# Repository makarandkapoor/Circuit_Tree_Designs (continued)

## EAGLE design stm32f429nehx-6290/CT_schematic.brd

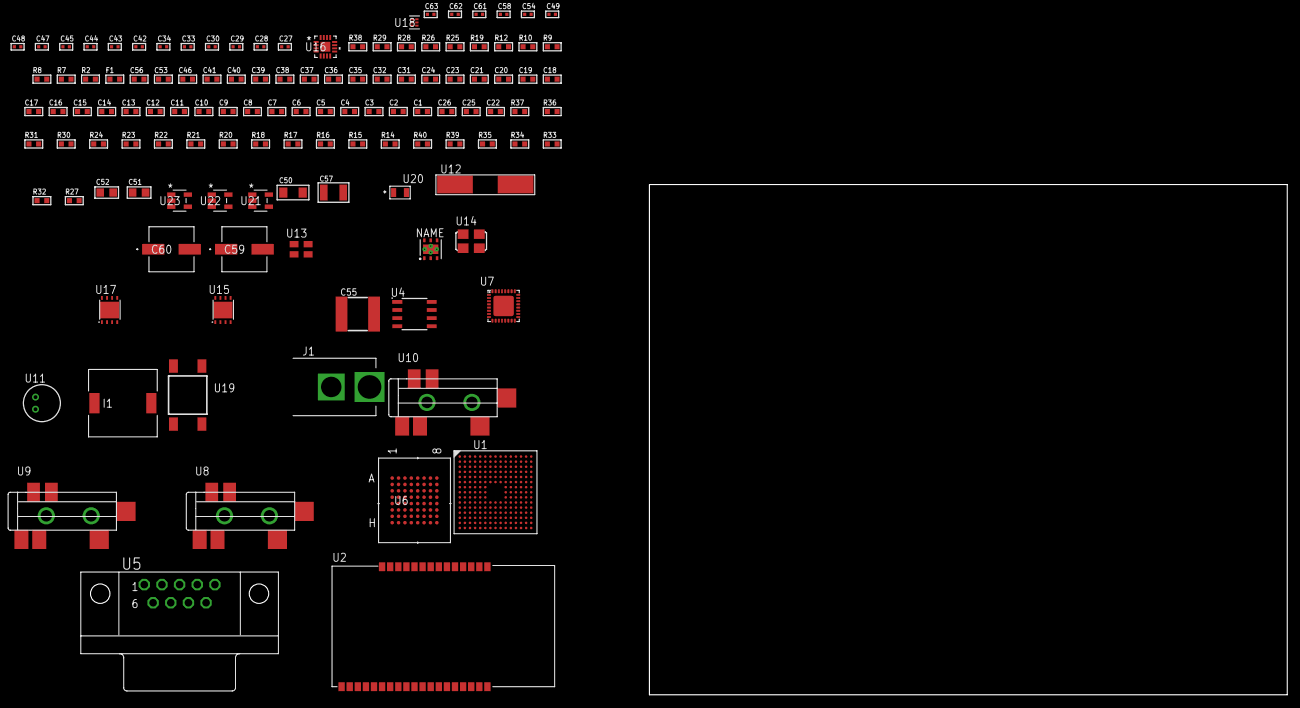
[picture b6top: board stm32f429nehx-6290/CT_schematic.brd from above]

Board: 2 copper layers, 100.0 x 80.0 mm, 122 parts (0 on the bottom side), 109 nets, no tracks yet.

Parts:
C1, C24, C31, C32, C35, C36, C37, C38, C39, C40, C41, C46, C53, C56: 1e-06; C0603
C2, C3, C4, C5, C6, C7, C8, C9, C10, C11, C12, C13, C14, C15, C16, C17, C18, C19, C20, C21: 1e-07; C0603
C22: 4.7e-06; C0603
C23: 1e-08; C0603
C25, C26: 2.2e-06; C0603
C27, C28: 1e-11; C0402
C29, C42, C43, C44, C45, C54, C58: 1e-07; C0402
C30, C33, C34, C47, C48, C49, C61, C62, C63: 1e-08; C0402
C50: 1e-05; C1206
C51, C52: 1e-05; C0805
C55: 6.8e-05; 2220
C57: 1e-05; C1210
C59, C60: 0.0001; EXV-9H
F1: 240.0; L0603
I1: 3.8e-06; DR1040
J1: PJ-037B; PJ-037B_PACKAGE
R2, R29: 1000.0; R0603
R7, R8, R9: 4700.0; R0603
R10, R12: 2200.0; R0603
R14, R15, R16, R17, R18, R20, R21, R22, R23, R24, R36, R37: 10000.0; R0603
R19: 120.0; R0603
R25, R26: 1270.0; R0603
R27, R33, R35: 100000.0; R0603
R28: 200.0; R0603
R30: 20000.0; R0603
R31: 91000.0; R0603
R32, R34: 300000.0; R0603
R38: 9100.0; R0603
R39: 680000.0; R0603
R40: 120000.0; R0603
U1: STM32F429NEH6; TFBGA216
U2: ETRX3587
U3: HDC1080DMBR; WSON-6
U4: MCP2562-E/SN; SOIC-8
U5: 182-009-113R531; 182-009-MALE
U6: mt28ew512aba1HPC-0AAT; LBGA-64
U7: SGTL5000XNAA3; QFN-32
U8, U9, U10: SJ-43515TS-SMT-TR
U11: WM-64PCT; WM-64PC
U12: ABLS-25.000MHZ-B2F-T
U13: ASEK-32.768KHz-ECST; ASEK
U14: ASFL-24.57MHZ-NCS; ASFL1
U15: LP3878SDX-ADJ/NOPB; WSON-8
U16: LTC3601EUD#PBF; QFN-16_EP
U17: LP2951ACSDX/NOPB; WSON-8
U18: TPS3895ADRYR; SON-6
U19: 4-1437565-2; SW_4-1437565-2
U20: Q65110A2395; LGM67K-G1J2-24-Z
U21, U22, U23: nc7sz125m5x; NC7SZ125M5X

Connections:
CLK_CRYSTAL_U1_G1: C27.1, U1.G1, U12.1
CLK_CRYSTAL_U1_H1: C28.1, U1.H1, U12.2
CLK_U1_E1: U1.E1, U13.3
CLK_U7_21: U7.21, U14.3
GND: C1.2, C2.2, C3.2, C4.2, C5.2, C6.2, C7.2, C8.2, C9.2, C10.2, C11.2, C12.2, C13.2, C14.2, C15.2, C16.2, C17.2, C18.2, C19.2, C20.2, C21.2, C22.2, C23.2, C24.2, C25.2, C26.2, C27.2, C28.2, C29.2, C30.2, C31.2, C32.2, C33.2, C34.2, C42.2, C43.2, C44.2, C45.2, C46.2, C47.2, C48.2, C49.2, C50.2, C51.2, C52.2, C53.2, C55.1, C55.2, C56.2, C57.2, C58.2, C59.2, C60.2, C61.2, C62.2, C63.2, J1.2, R2.2, R16.2, R17.2, R18.2, R26.2, R29.2, R30.2, R32.2, R35.2, R38.2, R40.2, U1.F2, U1.F6, U1.F7, U1.F8, U1.F9, U1.F10, U1.G6, U1.G10, U1.H6, U1.H10, U1.J6, U1.J10, U1.K6, U1.K7, U1.K8, U1.K9, U1.K10, U1.L6, U1.M1, U1.N1, U2.1, U2.13, U2.19, U2.20, U2.31, U2.33, U3.2, U3.PAD, U4.2, U4.8, U5.5, U6.E8, U6.H2, U6.H7, U7.1, U7.3, U7.7, U7.EXP, U9.1, U10.1, U11.2, U13.2, U14.2, U15.3, U15.PAD, U16.1, U16.9, U16.17, U17.3, U17.4, U17.PAD, U18.2, U20.C, U21.1, U21.3, U22.1, U22.3, U23.1, U23.3
NET_U1_A7: R10.1, U1.A7, U3.6
NET_U1_B4: R12.1, U1.B4, U3.1
NET_U1_E5: R14.1, U1.E5
NET_U1_E6: R15.1, U1.E6
NET_U1_E11: C26.1, U1.E11
NET_U1_J1: R9.1, U1.J1, U23.4
NET_U1_L5: R17.1, U1.L5
NET_U1_L11: C25.1, U1.L11
NET_U1_M5: R16.1, U1.M5
NET_U1_R1: C23.1, C24.1, F1.1, U1.P1, U1.R1
NET_U1_R15: U19.3, U19.4
NET_U2_7: R8.1, U2.7, U22.4
NET_U2_21: R18.1, U2.21
NET_U4_6: R19.2, U4.6
NET_U5_2: R19.2, U4.6, U5.2
NET_U5_3: R19.1, U4.7, U5.3
NET_U6_B4: R23.1, U6.B4
NET_U6_B5: R7.1, U6.B5, U21.4
NET_U7_10: C45.1, U7.10
NET_U7_29: R25.1, U7.29
NET_U7_31: R26.1, U7.31
NET_U8_1: U7.4, U8.1
NET_U8_2: U7.2, U8.2
NET_U8_5: U7.6, U8.5
NET_U9_2: C36.1, U9.2
NET_U9_5: C35.1, U9.5
NET_U10_2: C38.1, C39.1, U10.2
NET_U10_5: C37.1, U10.5
NET_U10_13: C38.2, C39.2
NET_U11_1: C40.1, C41.1, C46.1, U7.16, U11.1
NET_U11_15: C40.2, C41.2
NET_U15_1: C49.1, U15.1
NET_U15_6: R28.2, R29.1, U15.6
NET_U15_8: R27.1, U15.8
NET_U16_3: C54.2, I1.1, U16.3, U16.4
NET_U16_6: C54.1, U16.6
NET_U16_7: C53.1, U16.7, U16.12
NET_U16_10: R32.1, U16.10
NET_U16_11: R30.1, R31.1, U16.11
NET_U16_ATNET_3: I1.2, R31.2
NET_U17_5: R33.1, U17.5
NET_U17_7: R34.2, R35.1, U17.7
NET_U18_1: R37.1, R38.1, U18.1
NET_U18_3: R39.2, R40.1, U18.3
NET_U18_4: R36.1, U18.4, U21.2, U22.2, U23.2
NET_U19_1: R2.1, U19.1, U19.2
PROC_CAN1_RX: U1.C15, U4.4
PROC_CAN1_TX: U1.B15, U4.1
PROC_FMC_A0: U1.D2, U6.E2
PROC_FMC_A1: U1.E2, U6.D2
PROC_FMC_A2: U1.G2, U6.C2
PROC_FMC_A3: U1.H2, U6.A2
PROC_FMC_A4: U1.J2, U6.B2
PROC_FMC_A5: U1.K3, U6.D3
PROC_FMC_A6: U1.M6, U6.C3
PROC_FMC_A7: U1.N6, U6.A3
PROC_FMC_A8: U1.P6, U6.B6
PROC_FMC_A9: U1.M8, U6.A6
PROC_FMC_A10: U1.N7, U6.C6
PROC_FMC_A11: U1.M7, U6.D6
PROC_FMC_A12: U1.M13, U6.B7
PROC_FMC_A13: U1.M12, U6.A7
PROC_FMC_A14: U1.N12, U6.C7
PROC_FMC_A15: U1.N11, U6.D7
PROC_FMC_A16: U1.N10, U6.E7
PROC_FMC_A17: U1.M10, U6.B3
PROC_FMC_A18: U1.M11, U6.C4
PROC_FMC_A19: U1.A2, U6.D5
PROC_FMC_A20: U1.A1, U6.D4
PROC_FMC_A21: U1.B1, U6.C5
PROC_FMC_A22: U1.B2, U6.B8
PROC_FMC_A23: U1.A3, U6.C8
PROC_FMC_A24: U1.B3, U6.F8
PROC_FMC_D0: U1.L12, U6.E3
PROC_FMC_D1: U1.K13, U6.H3
PROC_FMC_D2: U1.B12, U6.E4
PROC_FMC_D3: U1.C12, U6.H4
PROC_FMC_D4: U1.R8, U6.H5
PROC_FMC_D5: U1.N9, U6.E5
PROC_FMC_D6: U1.P9, U6.H6
PROC_FMC_D7: U1.R9, U6.E6
PROC_FMC_D8: U1.P10, U6.F3
PROC_FMC_D9: U1.R10, U6.G3
PROC_FMC_D10: U1.R12, U6.F4
PROC_FMC_D11: U1.P11, U6.G4
PROC_FMC_D12: U1.R11, U6.F5
PROC_FMC_D13: U1.L15, U6.G6
PROC_FMC_D14: U1.L14, U6.F6
PROC_FMC_D15: U1.K15, U6.G7
PROC_FMC_NBL0: R24.1, U1.A6, U6.F7
PROC_FMC_NE2: R20.1, U1.D9, U6.F2
PROC_FMC_NOE: R21.1, U1.D11, U6.G2
PROC_FMC_NWAIT: U1.B11, U6.A4
PROC_FMC_NWE: R22.1, U1.C10, U6.A5
PROC_I2S2_CK: U1.C11, U7.24
PROC_I2S2_EXT_SD: U1.C14, U7.25
PROC_I2S2_SD: U1.C13, U7.26
PROC_I2S2_WS: U1.E14, U7.23
PROC_UART4_RX: U1.B13, U2.17
PROC_UART4_TX: U1.B14, U2.18
VCC_S1_9V2: C50.1, C52.1, C56.1, C59.1, C60.1, J1.1, R27.2, U15.4, U16.15, U16.16, U17.8
VCC_TIER1_1V2: C42.1, C51.1, R28.1, U7.30, U15.5
VCC_TIER1_3V3: C1.1, C2.1, C3.1, C4.1, C5.1, C6.1, C7.1, C8.1, C9.1, C10.1, C11.1, C12.1, C13.1, C14.1, C15.1, C16.1, C17.1, C18.1, C19.1, C20.1, C21.1, C22.1, C29.1, C30.1, C32.1, C33.1, C34.1, C43.1, C44.1, C47.1, C48.1, C55.2, C58.1, C61.1, C62.1, C63.1, F1.2, I1.2, R7.2, R8.2, R9.2, R10.2, R12.2, R14.2, R15.2, R20.2, R21.2, R22.2, R23.2, R24.2, R25.2, R31.2, R36.2, R37.2, R39.1, U1.C1, U1.E7, U1.E8, U1.E9, U1.E10, U1.F4, U1.F5, U1.F11, U1.G5, U1.G11, U1.H5, U1.H11, U1.J5, U1.J11, U1.K5, U1.K11, U1.L7, U1.L8, U1.L9, U1.L10, U2.32, U3.5, U4.5, U6.D8, U6.F1, U6.G5, U7.5, U7.20, U13.4, U14.4, U16.8, U18.6, U21.5, U22.5, U23.5
VCC_TIER1_5V0: C31.1, C57.1, R33.2, R34.1, U4.3, U17.1

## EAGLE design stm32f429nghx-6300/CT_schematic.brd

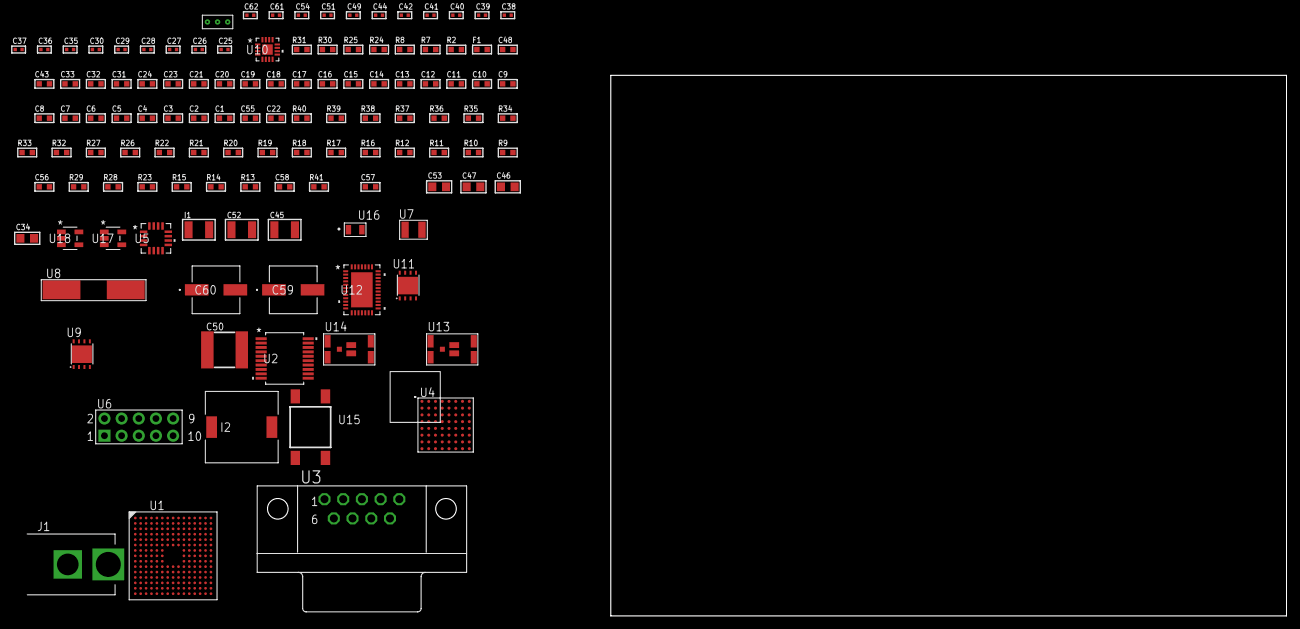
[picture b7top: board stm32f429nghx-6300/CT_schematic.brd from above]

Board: 2 copper layers, 100.0 x 80.0 mm, 121 parts (0 on the bottom side), 121 nets, no tracks yet.

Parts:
C1, C24, C31, C32, C33, C43, C48: 1e-06; C0603
C2, C3, C4, C5, C6, C7, C8, C9, C10, C11, C12, C13, C14, C15, C16, C17, C18, C19, C20, C21: 1e-07; C0603
C22: 4.7e-06; C0603
C23: 1e-08; C0603
C25, C26, C35, C37, C39, C41, C42, C49, C54: 1e-07; C0402
C27, C28, C29, C30: 1e-11; C0402
C34: 4.7e-06; C0805
C36, C38, C40, C44, C51, C61, C62: 1e-08; C0402
C45, C52: 1e-05; C1210
C46, C47, C53: 1e-05; C0805
C50: 6.8e-05; 2220
C55: 2.2e-06; C0603
C56: 2.45e-08; R0603
C57: 2.8258362168397e-09; R0603
C58: 7.105e-09; R0603
C59, C60: 0.0001; EXV-9H
F1: 240.0; L0603
I1: 1.5e-05; L1210
I2: 5.2e-06; DR1040
J1: PJ-037B; PJ-037B_PACKAGE
R2, R25, R31: 1000.0; R0603
R7, R8: 4700.0; R0603
R9, R10, R11, R12, R16, R17, R18, R19, R20, R21, R22, R32, R34, R35, R38, R39, R40: 10000.0; R0603
R13, R14, R15, R23, R29: 100000.0; R0603
R24, R30: 200.0; R0603
R26: 20000.0; R0603
R27: 62000.0; R0603
R28: 300000.0; R0603
R33: 75000.0; R0603
R36, R37: 95300.0; R0603
R41: 111363.63636364; R0603
U1: STM32F429NGH6; TFBGA216
U2: MAX3218EAP+T; SSOP-20
U3: 182-009-113R531; 182-009-MALE
U4: PC28F512P33BFD
U5: TSC2046IRGVR; VQFN-16
U6: HTSS-105-01-G-D
U7: ABS07-32.768KHZ-7-T
U8: ABLS-25.000MHZ-B2F-T
U9, U11: LP3878SDX-ADJ/NOPB; WSON-8
U10: LTC3601EUD#PBF; QFN-16_EP
U12: LTC2928CUHF#PBF; QFN-38_UHF
U13, U14: IRF8306MTRPbF; IRF8306MTRPBF
U15: 4-1437565-2; SW_4-1437565-2
U16: Q65110A2395; LGM67K-G1J2-24-Z
U17, U18: nc7sz125m5x; NC7SZ125M5X
U19: Dummy; DUMMY_PACKAGE_254

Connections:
CLK_CRYSTAL_U1_E1: C27.1, U1.E1, U7.1
CLK_CRYSTAL_U1_F1: C28.1, U1.F1, U7.2
CLK_CRYSTAL_U1_G1: C29.1, U1.G1, U8.1
CLK_CRYSTAL_U1_H1: C30.1, U1.H1, U8.2
GND: C1.2, C2.2, C3.2, C4.2, C5.2, C6.2, C7.2, C8.2, C9.2, C10.2, C11.2, C12.2, C13.2, C14.2, C15.2, C16.2, C17.2, C18.2, C19.2, C20.2, C21.2, C22.2, C23.2, C24.2, C25.2, C26.2, C27.2, C28.2, C29.2, C30.2, C31.2, C32.2, C33.2, C35.2, C36.2, C37.2, C38.2, C39.2, C40.2, C41.2, C42.2, C43.2, C44.2, C45.2, C46.2, C47.2, C48.2, C50.1, C50.2, C51.2, C52.2, C53.2, C54.2, C55.2, C56.2, C57.2, C58.2, C59.2, C60.2, C61.2, C62.2, J1.2, R2.2, R11.2, R25.2, R26.2, R28.2, R31.2, R33.2, R36.2, R37.2, R38.2, R39.2, R40.2, U1.F2, U1.F6, U1.F7, U1.F8, U1.F9, U1.F10, U1.G6, U1.G10, U1.H6, U1.H10, U1.J6, U1.J10, U1.K6, U1.K7, U1.K8, U1.K9, U1.K10, U1.L6, U1.M1, U1.N1, U2.5, U2.17, U2.20, U3.5, U4.B2, U4.H2, U4.H4, U4.H6, U5.10, U6.9, U9.3, U9.PAD, U10.1, U10.9, U10.17, U11.3, U11.PAD, U12.8, U12.9, U12.10, U12.12, U12.13, U12.24, U12.25, U12.30, U12.32, U12.39, U16.C, U17.1, U17.3, U18.1, U18.3, U19.1
NET_U1_E5: R9.1, U1.E5
NET_U1_E6: R10.1, U1.E6
NET_U1_E11: C26.1, U1.E11
NET_U1_J1: R8.1, U1.J1, U18.4
NET_U1_L5: R12.1, U1.L5
NET_U1_M5: R11.1, U1.M5
NET_U1_R1: C23.1, C24.1, F1.1, U1.P1, U1.R1
NET_U1_R15: U15.3, U15.4
NET_U2_1: I1.1, U2.1
NET_U2_2: R13.1, U2.2
NET_U2_3: R14.1, U2.3
NET_U2_4: R15.1, U2.4
NET_U2_15: C33.1, U2.15
NET_U2_16: C34.2, U2.16
NET_U2_18: C34.1, U2.18
NET_U2_19: C32.1, U2.19
NET_U3_2: U2.12, U3.2
NET_U3_3: U2.14, U3.3
NET_U3_7: U2.11, U3.7
NET_U3_8: U2.13, U3.8
NET_U4_A4: C39.1, C40.1, U4.A4
NET_U4_C6: R19.1, U4.C6
NET_U4_D4: R7.1, U4.D4, U17.4
NET_U5_15: R22.1, U5.15
NET_U6_3: U5.7, U6.3
NET_U6_4: U5.9, U6.4
NET_U6_5: U5.6, U6.5
NET_U6_6: U5.8, U6.6
NET_U9_1: C44.1, U9.1
NET_U9_6: R24.2, R25.1, U9.6
NET_U9_8: R23.1, U9.8
NET_U10_3: C49.2, I2.1, U10.3, U10.4
NET_U10_6: C49.1, U10.6
NET_U10_7: C48.1, U10.7, U10.12
NET_U10_10: R28.1, U10.10
NET_U10_11: R26.1, R27.1, U10.11
NET_U10_ATNET_3: I2.2, R27.2
NET_U11_1: C51.1, U11.1
NET_U11_6: R30.2, R31.1, U11.6
NET_U11_8: R29.1, U11.8
NET_U12_3: R39.1, U12.3
NET_U12_6: R36.1, U12.6
NET_U12_7: R37.1, U12.7
NET_U12_16: R38.1, R41.1, U12.16
NET_U12_18: R35.1, U12.18
NET_U12_19: R34.1, U12.19, U12.20
NET_U12_21: R32.1, R33.1, U12.21, U17.2, U18.2
NET_U12_22: C54.1, R32.2, R34.2, R35.2, U12.11, U12.22
NET_U12_26: C57.1, U12.26
NET_U12_27: C56.1, U12.27
NET_U12_28: C58.1, U12.28
NET_U12_38: R40.1, U12.38
NET_U13_3: U12.2, U13.3
NET_U14_3: U12.37, U14.3
NET_U15_1: R2.1, U15.1, U15.2
PROC_ADC1_IN3: U1.R2, U19.2
PROC_ADC1_IN4: U1.N4, U19.3
PROC_FMC_A0: U1.D2, U4.A1
PROC_FMC_A1: U1.E2, U4.B1
PROC_FMC_A2: U1.G2, U4.C1
PROC_FMC_A3: U1.H2, U4.D1
PROC_FMC_A4: U1.J2, U4.D2
PROC_FMC_A5: U1.K3, U4.A2
PROC_FMC_A6: U1.M6, U4.C2
PROC_FMC_A7: U1.N6, U4.A3
PROC_FMC_A8: U1.P6, U4.B3
PROC_FMC_A9: U1.M8, U4.C3
PROC_FMC_A10: U1.N7, U4.D3
PROC_FMC_A11: U1.M7, U4.C4
PROC_FMC_A12: U1.M13, U4.A5
PROC_FMC_A13: U1.M12, U4.B5
PROC_FMC_A14: U1.N12, U4.C5
PROC_FMC_A15: U1.N11, U4.D7
PROC_FMC_A16: U1.N10, U4.D8
PROC_FMC_A17: U1.M10, U4.A7
PROC_FMC_A18: U1.M11, U4.B7
PROC_FMC_A19: U1.A2, U4.C7
PROC_FMC_A20: U1.A1, U4.C8
PROC_FMC_A21: U1.B1, U4.A8
PROC_FMC_A22: U1.B2, U4.G1
PROC_FMC_A23: U1.A3, U4.H8
PROC_FMC_A24: U1.B3, U4.B6
PROC_FMC_CLK: U1.C11, U4.E6
PROC_FMC_D0: U1.L12, U4.F2
PROC_FMC_D1: U1.K13, U4.E2
PROC_FMC_D2: U1.B12, U4.G3
PROC_FMC_D3: U1.C12, U4.E4
PROC_FMC_D4: U1.R8, U4.E5
PROC_FMC_D5: U1.N9, U4.G5
PROC_FMC_D6: U1.P9, U4.G6
PROC_FMC_D7: U1.R9, U4.H7
PROC_FMC_D8: U1.P10, U4.E1
PROC_FMC_D9: U1.R10, U4.E3
PROC_FMC_D10: U1.R12, U4.F3
PROC_FMC_D11: U1.P11, U4.F4
PROC_FMC_D12: U1.R11, U4.F5
PROC_FMC_D13: U1.L15, U4.H5
PROC_FMC_D14: U1.L14, U4.G7
PROC_FMC_D15: U1.K15, U4.E7
PROC_FMC_NE2: R17.1, U1.D9, U4.B4
PROC_FMC_NL: R16.1, U1.B5, U4.F6
PROC_FMC_NOE: R18.1, U1.D11, U4.F8
PROC_FMC_NWAIT: U1.B11, U4.F7
PROC_FMC_NWE: R20.1, U1.C10, U4.G8
PROC_SPI1_MISO: U1.A9, U5.16
PROC_SPI1_MOSI: U1.A8, U5.2
PROC_SPI1_NSS: R21.1, U1.A13, U5.3
PROC_SPI1_SCK: U1.A10, U5.4
PROC_UART4_RX: U1.B13, U2.9
PROC_UART4_TX: U1.B14, U2.7
VCC_13V6: C55.1, C59.1, C60.1, J1.1, R41.2, U12.23, U13.1, U13.2, U13.6, U13.7, U14.1, U14.2, U14.6, U14.7
VCC_S1_13V6: C45.1, C47.1, R23.2, U9.4, U10.15, U10.16, U13.4, U13.5
VCC_S2_13V6: C52.1, R29.2, U11.4, U14.4, U14.5
VCC_TIER1_1V2: C25.1, C46.1, R24.1, U1.L11, U9.5
VCC_TIER1_2V5: C1.1, C2.1, C3.1, C4.1, C5.1, C6.1, C7.1, C8.1, C9.1, C10.1, C11.1, C12.1, C13.1, C14.1, C15.1, C16.1, C17.1, C18.1, C19.1, C20.1, C21.1, C22.1, C31.1, C35.1, C36.1, C37.1, C38.1, C41.1, C42.1, C43.1, C50.2, C61.1, C62.1, F1.2, I1.2, I2.2, R7.2, R8.2, R9.2, R10.2, R12.2, R13.2, R14.2, R15.2, R16.2, R17.2, R18.2, R19.2, R20.2, R21.2, R22.2, R27.2, U1.C1, U1.E7, U1.E8, U1.E9, U1.E10, U1.F4, U1.F5, U1.F11, U1.G5, U1.G11, U1.H5, U1.H11, U1.J5, U1.J11, U1.K5, U1.K11, U1.L7, U1.L8, U1.L9, U1.L10, U2.6, U4.A6, U4.D5, U4.D6, U4.G4, U4.H3, U5.5, U5.14, U10.8, U17.5, U18.5
VCC_TIER2_1V2: C53.1, R30.1, U11.5

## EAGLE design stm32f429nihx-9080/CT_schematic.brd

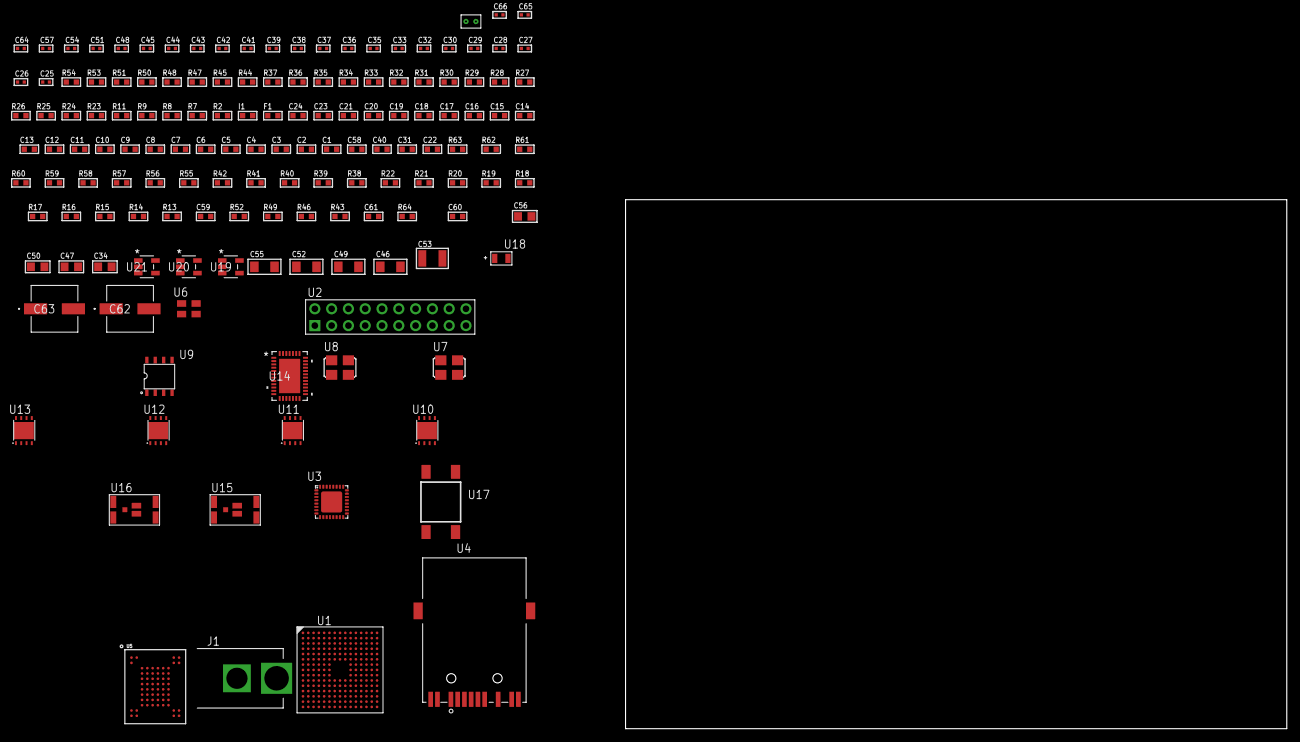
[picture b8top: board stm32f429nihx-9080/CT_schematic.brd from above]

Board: 2 copper layers, 100.0 x 80.0 mm, 148 parts (0 on the bottom side), 100 nets, no tracks yet.

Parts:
C1, C24: 1e-06; C0603
C2, C3, C4, C5, C6, C7, C8, C9, C10, C11, C12, C13, C14, C15, C16, C17, C18, C19, C20, C21: 1e-07; C0603
C22: 4.7e-06; C0603
C23: 1e-08; C0603
C25, C26, C27, C28, C29, C30, C32, C33, C35, C36, C37, C38, C39, C57: 1e-07; C0402
C31, C40, C58: 2.2e-06; C0603
C34, C47, C50, C56: 1e-05; C0805
C41, C42, C43, C44, C45, C48, C51, C54, C64, C65, C66: 1e-08; C0402
C46, C49, C52, C55: 1e-05; C1206
C53: 1e-05; C1210
C59: 2.45e-08; R0603
C60: 2.8258362168397e-09; R0603
C61: 7.105e-09; R0603
C62, C63: 0.0001; EXV-9H
F1: 240.0; L0603
I1: 97.0; R0603
J1: PJ-037B; PJ-037B_PACKAGE
R2, R32, R34, R35, R45, R48, R51, R54: 1000.0; R0603
R7, R8, R28, R29, R30, R31, R33, R36, R37: 4700.0; R0603
R9, R11: 2200.0; R0603
R13, R14, R15, R16, R17, R18, R19, R20, R21, R22, R38, R39, R40, R41, R42, R55, R57, R58, R61, R62, R63: 10000.0; R0603
R23, R24: 0.1; R0603
R25, R44, R53: 200.0; R0603
R26: 220.0; R0603
R27: 6490.0; R0603
R43, R46, R49, R52: 100000.0; R0603
R47: 806.0; R0603
R50: 2231.0; R0603
R56: 75000.0; R0603
R59, R60: 95300.0; R0603
R64: 52563.636363636; R0603
U1: STM32F429NIH7; TFBGA216
U2: TST-110-05-T-D-RA
U3: KSZ8081RNBIA-TR; QFN-32
U4: 7498011122R
U5: mt29f4g08abbdah4; VFBGA-63
U6: ASEK-32.768KHz-ECST; ASEK
U7: ASFL1-25MHZ-NCS; ASFL1
U8: ASFL1-50MHZ-NCS; ASFL1
U9: idt74fct38072; IDT74FCT38072
U10, U11, U12, U13: LP3878SDX-ADJ/NOPB; WSON-8
U14: LTC2928CUHF#PBF; QFN-38_UHF
U15, U16: IRF8306MTRPbF; IRF8306MTRPBF
U17: 4-1437565-2; SW_4-1437565-2
U18: Q65110A2395; LGM67K-G1J2-24-Z
U19, U20, U21: nc7sz125m5x; NC7SZ125M5X
U22: Dummy; DUMMY_PACKAGE_318

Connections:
CLK_U1_E1: U1.E1, U6.3
CLK_U1_G1: U1.G1, U7.3
CLK_U1_N2: U1.N2, U9.7
CLK_U3_9: U3.9, U9.6
CLK_U9_3: U8.3, U9.3
GND: C1.2, C2.2, C3.2, C4.2, C5.2, C6.2, C7.2, C8.2, C9.2, C10.2, C11.2, C12.2, C13.2, C14.2, C15.2, C16.2, C17.2, C18.2, C19.2, C20.2, C21.2, C22.2, C23.2, C24.2, C25.2, C26.2, C27.2, C28.2, C29.2, C30.2, C31.2, C32.2, C33.2, C34.2, C35.2, C36.2, C37.2, C38.2, C39.2, C40.2, C41.2, C42.2, C43.2, C44.2, C45.2, C46.2, C47.2, C48.2, C49.2, C50.2, C51.2, C52.2, C53.2, C54.2, C55.2, C56.2, C57.2, C58.2, C59.2, C60.2, C61.2, C62.2, C63.2, C64.2, C65.2, C66.2, J1.2, R2.2, R15.2, R22.2, R23.2, R24.2, R27.2, R29.2, R32.2, R34.2, R35.2, R45.2, R48.2, R51.2, R54.2, R56.2, R59.2, R60.2, R61.2, R62.2, R63.2, U1.F2, U1.F6, U1.F7, U1.F8, U1.F9, U1.F10, U1.G6, U1.G10, U1.H6, U1.H10, U1.J6, U1.J10, U1.K6, U1.K7, U1.K8, U1.K9, U1.K10, U1.L6, U1.M1, U1.N1, U2.4, U2.6, U2.8, U2.10, U2.12, U2.14, U2.16, U2.18, U2.20, U3.1, U3.EXP, U4.1, U4.10, U5.C5, U5.F7, U5.K3, U5.K8, U6.2, U7.2, U8.2, U9.4, U9.5, U9.8, U10.3, U10.PAD, U11.3, U11.PAD, U12.3, U12.PAD, U13.3, U13.PAD, U14.8, U14.9, U14.10, U14.12, U14.13, U14.24, U14.25, U14.30, U14.32, U14.39, U18.C, U19.2, U19.3, U20.1, U20.3, U21.1, U21.3, U22.1
NET_U1_E5: R13.1, U1.E5
NET_U1_E6: R14.1, U1.E6
NET_U1_E11: C26.1, U1.E11
NET_U1_J1: R8.1, U1.J1, U21.4
NET_U1_L5: R16.1, U1.L5
NET_U1_M3: R9.1, U1.M3, U3.12
NET_U1_M5: R15.1, U1.M5
NET_U1_P2: R11.1, U1.P2, U3.11
NET_U1_R1: C23.1, C24.1, F1.1, U1.P1, U1.R1
NET_U1_R15: U17.3, U17.4
NET_U2_19: R22.1, U2.19
NET_U3_2: C31.1, C32.1, U3.2
NET_U3_3: C33.1, I1.1, U3.3
NET_U3_10: R27.1, U3.10
NET_U3_13: R30.1, U3.13
NET_U3_14: R31.1, U3.14
NET_U3_19: R29.1, U3.19
NET_U3_20: R35.1, U3.20
NET_U3_21: R28.1, U3.21
NET_U3_28: R33.1, U3.28
NET_U3_29: R34.1, U3.29
NET_U3_31: R36.1, U3.31
NET_U3_32: R7.1, U3.32, U20.4
NET_U4_1: U3.7, U4.1
NET_U4_2: C29.1, U4.2
NET_U4_3: U3.6, U4.3
NET_U4_4: U3.5, U4.4
NET_U4_5: C30.1, U4.5
NET_U4_6: U3.4, U4.6
NET_U4_8: R24.1, U4.8
NET_U4_9: R25.1, U4.9
NET_U4_12: R26.1, U4.12
NET_U4_13: R23.1, U4.13, U4.14
NET_U5_C3: R42.1, U5.C3
NET_U10_1: C45.1, U10.1
NET_U10_6: R44.2, R45.1, U10.6
NET_U10_8: R43.1, U10.8
NET_U11_1: C48.1, U11.1
NET_U11_6: R47.2, R48.1, U11.6
NET_U11_8: R46.1, U11.8
NET_U12_1: C51.1, U12.1
NET_U12_6: R50.2, R51.1, U12.6
NET_U12_8: R49.1, U12.8
NET_U13_1: C54.1, U13.1
NET_U13_6: R53.2, R54.1, U13.6
NET_U13_8: R52.1, U13.8
NET_U14_3: R62.1, U14.3
NET_U14_6: R59.1, U14.6
NET_U14_7: R60.1, U14.7
NET_U14_16: R61.1, R64.1, U14.16
NET_U14_18: R58.1, U14.18
NET_U14_19: R57.1, U14.19, U14.20
NET_U14_21: R55.1, R56.1, U14.21, U19.4, U20.2, U21.2
NET_U14_26: C60.1, U14.26
NET_U14_27: C59.1, U14.27
NET_U14_28: C61.1, U14.28
NET_U14_38: R63.1, U14.38
NET_U15_3: U14.2, U15.3
NET_U16_3: U14.37, U16.3
NET_U17_1: R2.1, U17.1, U17.2
PROC_DAC_OUT2: U1.P4, U22.2
PROC_ETH_CRS_DV: U1.R3, U3.18
PROC_ETH_RXD0: R37.1, U1.N5, U3.16
PROC_ETH_RXD1: R32.1, U1.P5, U3.15
PROC_ETH_TXD0: U1.B3, U3.24
PROC_ETH_TXD1: U1.A4, U3.25
PROC_ETH_TX_EN: U1.B8, U3.23
PROC_FMC_A16: U1.N10, U5.D5
PROC_FMC_A17: U1.M10, U5.C4
PROC_FMC_D0: U1.L12, U5.H4
PROC_FMC_D1: U1.K13, U5.J4
PROC_FMC_D2: U1.B12, U5.K4
PROC_FMC_D3: U1.C12, U5.K5
PROC_FMC_D4: U1.R8, U5.K6
PROC_FMC_D5: U1.N9, U5.J7
PROC_FMC_D6: U1.P9, U5.K7
PROC_FMC_D7: U1.R9, U5.J8
PROC_FMC_INT2: R38.1, U1.J15, U5.C8
PROC_FMC_NCE2: R39.1, U1.A11, U5.C6
PROC_FMC_NOE: R41.1, U1.D11, U5.D4
PROC_FMC_NWE: R40.1, U1.C10, U5.C7
PROC_SYS_JTCK_SWCLK: R20.1, U1.A14, U2.9
PROC_SYS_JTDI: R18.1, U1.A13, U2.5
PROC_SYS_JTDO_SWO: U1.A10, U2.13
PROC_SYS_JTMS_SWDIO: R19.1, U1.A15, U2.7
PROC_SYS_JTRST: R17.1, U1.A9, U2.3
RST_OUT_U2_SRESET_B: R21.1, U2.15, U19.1
VCC_7V0: C57.1, C58.1, C62.1, C63.1, J1.1, R55.2, R57.2, R58.2, R64.2, U14.11, U14.22, U15.1, U15.2, U15.6, U15.7, U16.1, U16.2, U16.6, U16.7
VCC_S1_7V0: C46.1, C49.1, C52.1, R43.2, R46.2, R49.2, U10.4, U11.4, U12.4, U15.4, U15.5
VCC_S2_7V0: C55.1, R52.2, U13.4, U16.4, U16.5
VCC_TIER1_1V2: C25.1, C47.1, R44.1, U1.L11, U10.5
VCC_TIER1_1V8: C1.1, C2.1, C3.1, C4.1, C5.1, C6.1, C7.1, C8.1, C9.1, C10.1, C11.1, C12.1, C13.1, C14.1, C15.1, C16.1, C17.1, C18.1, C19.1, C20.1, C21.1, C22.1, C28.1, C34.1, C35.1, C36.1, C37.1, C38.1, C39.1, C40.1, C50.1, C64.1, C65.1, C66.1, F1.2, R7.2, R8.2, R9.2, R11.2, R13.2, R14.2, R16.2, R17.2, R18.2, R19.2, R20.2, R21.2, R28.2, R30.2, R31.2, R33.2, R36.2, R37.2, R38.2, R39.2, R40.2, R41.2, R42.2, R47.1, U1.C1, U1.E7, U1.E8, U1.E9, U1.E10, U1.F4, U1.F5, U1.F11, U1.G5, U1.G11, U1.H5, U1.H11, U1.J5, U1.J11, U1.K5, U1.K11, U1.L7, U1.L8, U1.L9, U1.L10, U2.1, U3.17, U5.D3, U5.G4, U5.H8, U5.J6, U11.5, U19.5, U20.5, U21.5
VCC_TIER1_3V3: C27.1, C41.1, C42.1, C43.1, C44.1, C53.1, I1.2, R50.1, U2.2, U6.4, U7.4, U8.4, U9.1, U9.2, U12.5
VCC_TIER2_1V2: C56.1, R53.1, U13.5
